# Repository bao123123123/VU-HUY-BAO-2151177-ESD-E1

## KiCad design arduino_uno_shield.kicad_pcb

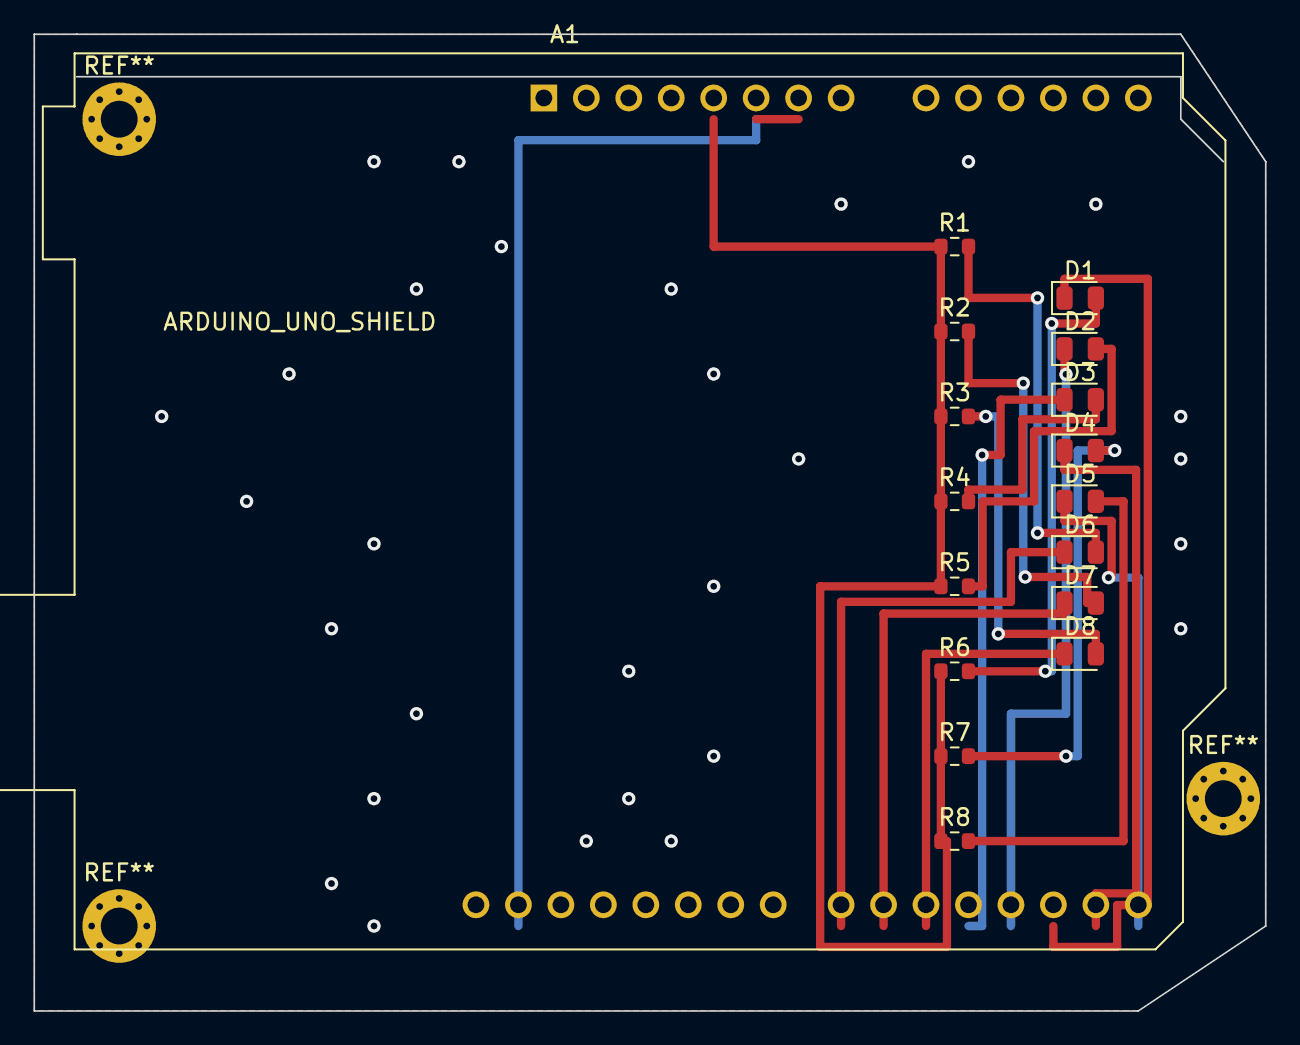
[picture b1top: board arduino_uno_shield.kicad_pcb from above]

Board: 2 copper layers, 73.7 x 58.4 mm, 17 parts (0 on the bottom side), 18 nets.

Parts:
A1: Arduino_UNO_R2
D1, D2, D3, D4, D5, D6, D7, D8: LED; LED_0805_2012Metric
R1, R2, R3, R4, R5, R6, R7, R8: 247; R_0603_1608Metric

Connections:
GND: A1.6 (GND), A1.7 (GND), A1.29 (GND)
unnamed: A1.5 (+5V), R1.1, R2.1, R3.1, R4.1, R5.1, R6.1, R7.1, R8.1
unnamed: A1.15 (D0/RX), D5.1 (K)
unnamed: A1.16 (D1/TX), D4.1 (K)
unnamed: A1.17 (D2), D1.1 (K)
unnamed: A1.18 (D3), D2.1 (K)
unnamed: A1.19 (D4), D3.1 (K)
unnamed: A1.20 (D5), D8.1 (K)
unnamed: A1.21 (D6), D7.1 (K)
unnamed: A1.22 (D7), D6.1 (K)
unnamed: D1.2 (A), R6.2
unnamed: D2.2 (A), R5.2
unnamed: D3.2 (A), R4.2
unnamed: D4.2 (A), R7.2
unnamed: D5.2 (A), R8.2
unnamed: D6.2 (A), R1.2
unnamed: D7.2 (A), R2.2
unnamed: D8.2 (A), R3.2

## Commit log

2024-01-18 init project
